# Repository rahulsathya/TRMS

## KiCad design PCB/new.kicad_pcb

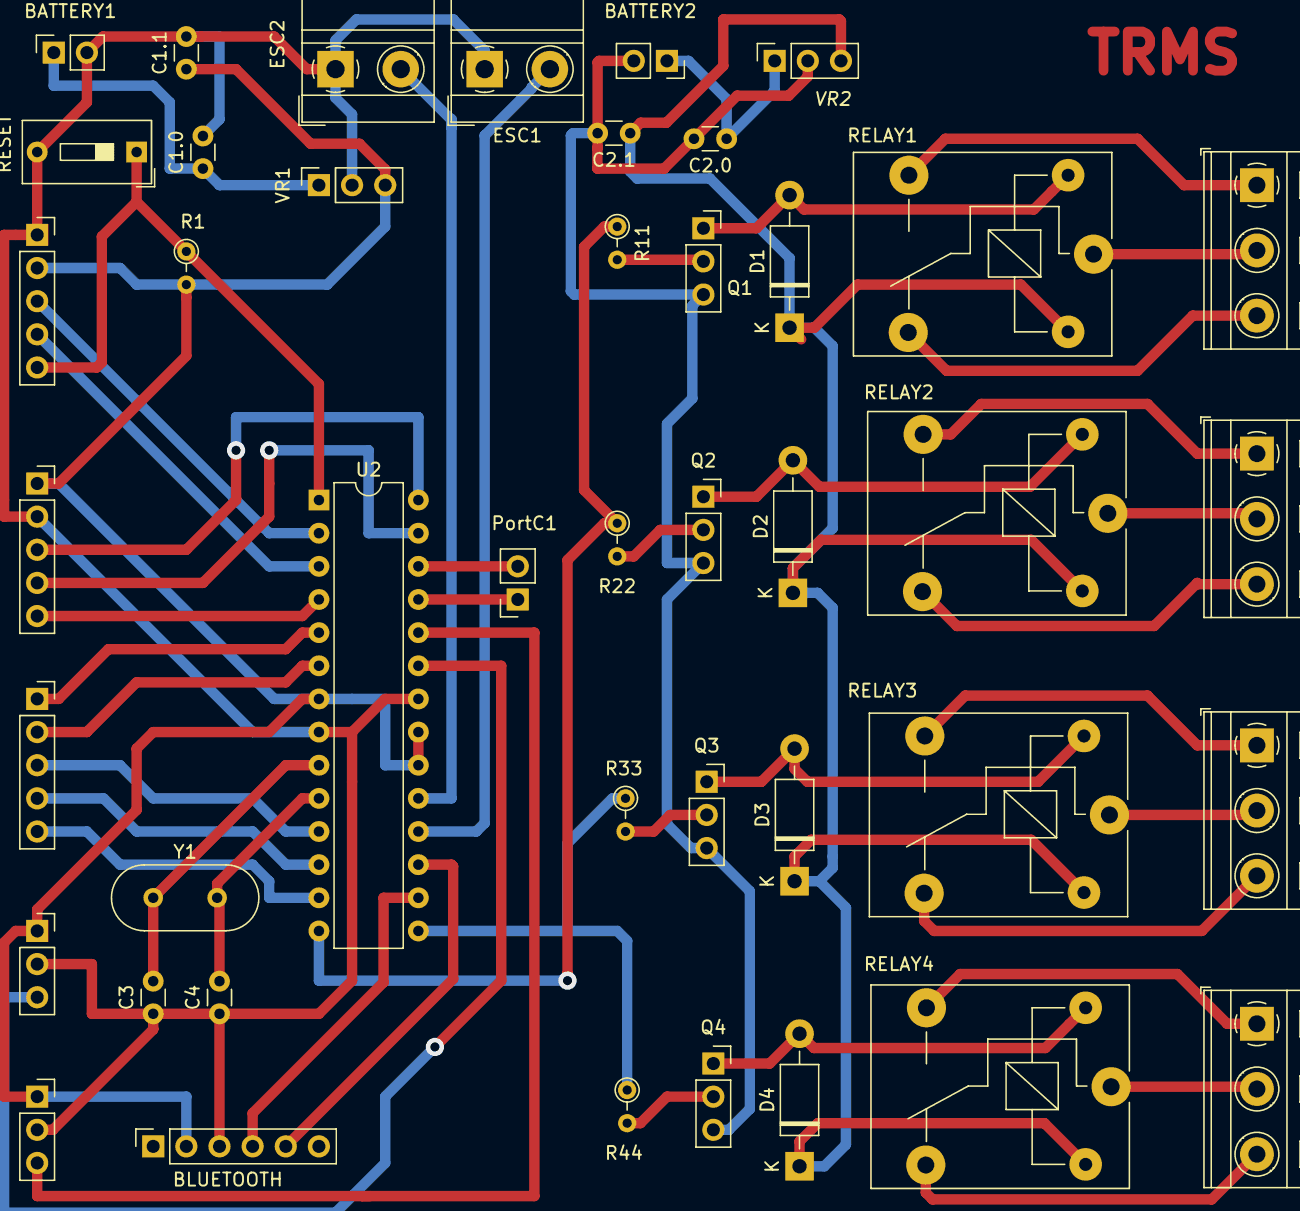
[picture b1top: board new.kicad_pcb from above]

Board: 2 copper layers, 43 parts (0 on the bottom side), 49 nets.

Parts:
BATTERY1: BATTERY1; PinSocket_1x02_P2.54mm_Vertical
BATTERY2: BATTERY2; PinSocket_1x02_P2.54mm_Vertical
BLUETOOTH: BLUETOOTH; PinSocket_1x06_P2.54mm_Vertical
C1.0, C1.1: CP1; C_Disc_D3.0mm_W1.6mm_P2.50mm
C2.0, C2.1: CP2; C_Disc_D3.0mm_W1.6mm_P2.50mm
C3, C4: C; C_Disc_D3.0mm_W1.6mm_P2.50mm
D1, D2: D; D_DO-41_SOD81_P10.16mm_Horizontal
D3: D3; D_DO-41_SOD81_P10.16mm_Horizontal
D4: D4; D_DO-41_SOD81_P10.16mm_Horizontal
ESC1: ESC1; TerminalBlock_MetzConnect_Type011_RT05502HBWC_1x02_P5.00mm_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
ESC2: ESC2; TerminalBlock_MetzConnect_Type011_RT05502HBWC_1x02_P5.00mm_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
MPU6050: .; PinSocket_1x05_P2.54mm_Vertical
PortC1: _; PinSocket_1x02_P2.54mm_Vertical
PortD1: _; PinSocket_1x05_P2.54mm_Vertical
Q1, Q2, Q3, Q4: BC547; PinSocket_1x03_P2.54mm_Vertical
R1, R11, R22, R33, R44: R; R_Axial_DIN0204_L3.6mm_D1.6mm_P2.54mm_Vertical
RELAY1: RELAY1; Relay_SPDT_SANYOU_SRD_Series_Form_C
RELAY2: RELAY2; Relay_SPDT_SANYOU_SRD_Series_Form_C
RELAY3: RELAY3; Relay_SPDT_SANYOU_SRD_Series_Form_C
RELAY4: RELAY4; Relay_SPDT_SANYOU_SRD_Series_Form_C
RESET: RESET; SW_DIP_SPSTx01_Slide_9.78x4.72mm_W7.62mm_P2.54mm
RPM1: j1; PinSocket_1x03_P2.54mm_Vertical
RPM2: RPM2; PinSocket_1x03_P2.54mm_Vertical
TERMINAL1: S1; TerminalBlock_MetzConnect_Type094_RT03503HBLU_1x03_P5.00mm_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
TERMINAL2: S2; TerminalBlock_MetzConnect_Type094_RT03503HBLU_1x03_P5.00mm_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
TERMINAL3: S3; TerminalBlock_MetzConnect_Type094_RT03503HBLU_1x03_P5.00mm_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
TERMINAL4: S4; TerminalBlock_MetzConnect_Type094_RT03503HBLU_1x03_P5.00mm_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
U2: ATmega328-PU; DIP-28_W7.62mm
USB: USB; PinSocket_1x05_P2.54mm_Vertical
VR1, VR2: L7805; PinSocket_1x03_P2.54mm_Vertical
Y1: Crystal; Crystal_HC18-U_Vertical

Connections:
GND: BATTERY1.2, BLUETOOTH.3, C1.0.2, C1.1.2, C3.1, C4.1, ESC1.1, ESC2.1, MPU6050.2, RESET.2, RPM1.2, RPM2.2, U2.8, U2.22, USB.1, VR1.2
unnamed: BLUETOOTH.2, C1.1.1, MPU6050.1, R1.2, RPM1.1, RPM2.1, U2.7, U2.20, U2.21, USB.2, VR1.3
unnamed: U2.2, USB.3
unnamed: U2.3, USB.4
unnamed: R1.1, RESET.1, U2.1, USB.5
unnamed: BATTERY1.1, C1.0.1, VR1.1
unnamed: BATTERY2.1, C2.0.1, VR2.1
unnamed: BATTERY2.2, C2.0.2, C2.1.2, Q1.3, Q2.3, Q3.3, Q4.3, VR2.2
unnamed: C2.1.1, D1.1, D2.1, D3.1, D4.1, RELAY1.5, RELAY2.5, RELAY3.5, RELAY4.5, VR2.3
unnamed: C3.2, U2.9, Y1.1
unnamed: C4.2, U2.10, Y1.2
unnamed: D1.2, Q1.1, RELAY1.2
unnamed: D2.2, Q2.1, RELAY2.2
unnamed: D3.2, Q3.1, RELAY3.2
unnamed: D4.2, Q4.1, RELAY4.2
unnamed: RPM1.3, U2.23
unnamed: RPM2.3, U2.24
unnamed: ESC1.2, U2.18
unnamed: ESC2.2, U2.19
unnamed: RELAY1.3, TERMINAL1.1
unnamed: RELAY1.1, TERMINAL1.2
unnamed: RELAY1.4, TERMINAL1.3
unnamed: BLUETOOTH.4, U2.16
unnamed: BLUETOOTH.5, U2.17
unnamed: RELAY2.3, TERMINAL2.1
unnamed: RELAY2.1, TERMINAL2.2
unnamed: RELAY2.4, TERMINAL2.3
unnamed: RELAY3.3, TERMINAL3.1
unnamed: RELAY3.1, TERMINAL3.2
unnamed: RELAY3.4, TERMINAL3.3
unnamed: RELAY4.3, TERMINAL4.1
unnamed: RELAY4.1, TERMINAL4.2
unnamed: RELAY4.4, TERMINAL4.3
unnamed: MPU6050.3, U2.28
unnamed: MPU6050.4, U2.27
unnamed: MPU6050.5, U2.4
unnamed: PortC1.1, U2.25
unnamed: PortC1.2, U2.26
unnamed: PortD1.1, U2.5
unnamed: PortD1.2, U2.6
unnamed: PortD1.3, U2.11
unnamed: PortD1.4, U2.12
unnamed: PortD1.5, U2.13
unnamed: Q1.2, R11.2
unnamed: Q2.2, R22.2
unnamed: Q3.2, R33.2
unnamed: Q4.2, R44.2
unnamed: R11.1, R22.1, U2.14
unnamed: R33.1, R44.1, U2.15
